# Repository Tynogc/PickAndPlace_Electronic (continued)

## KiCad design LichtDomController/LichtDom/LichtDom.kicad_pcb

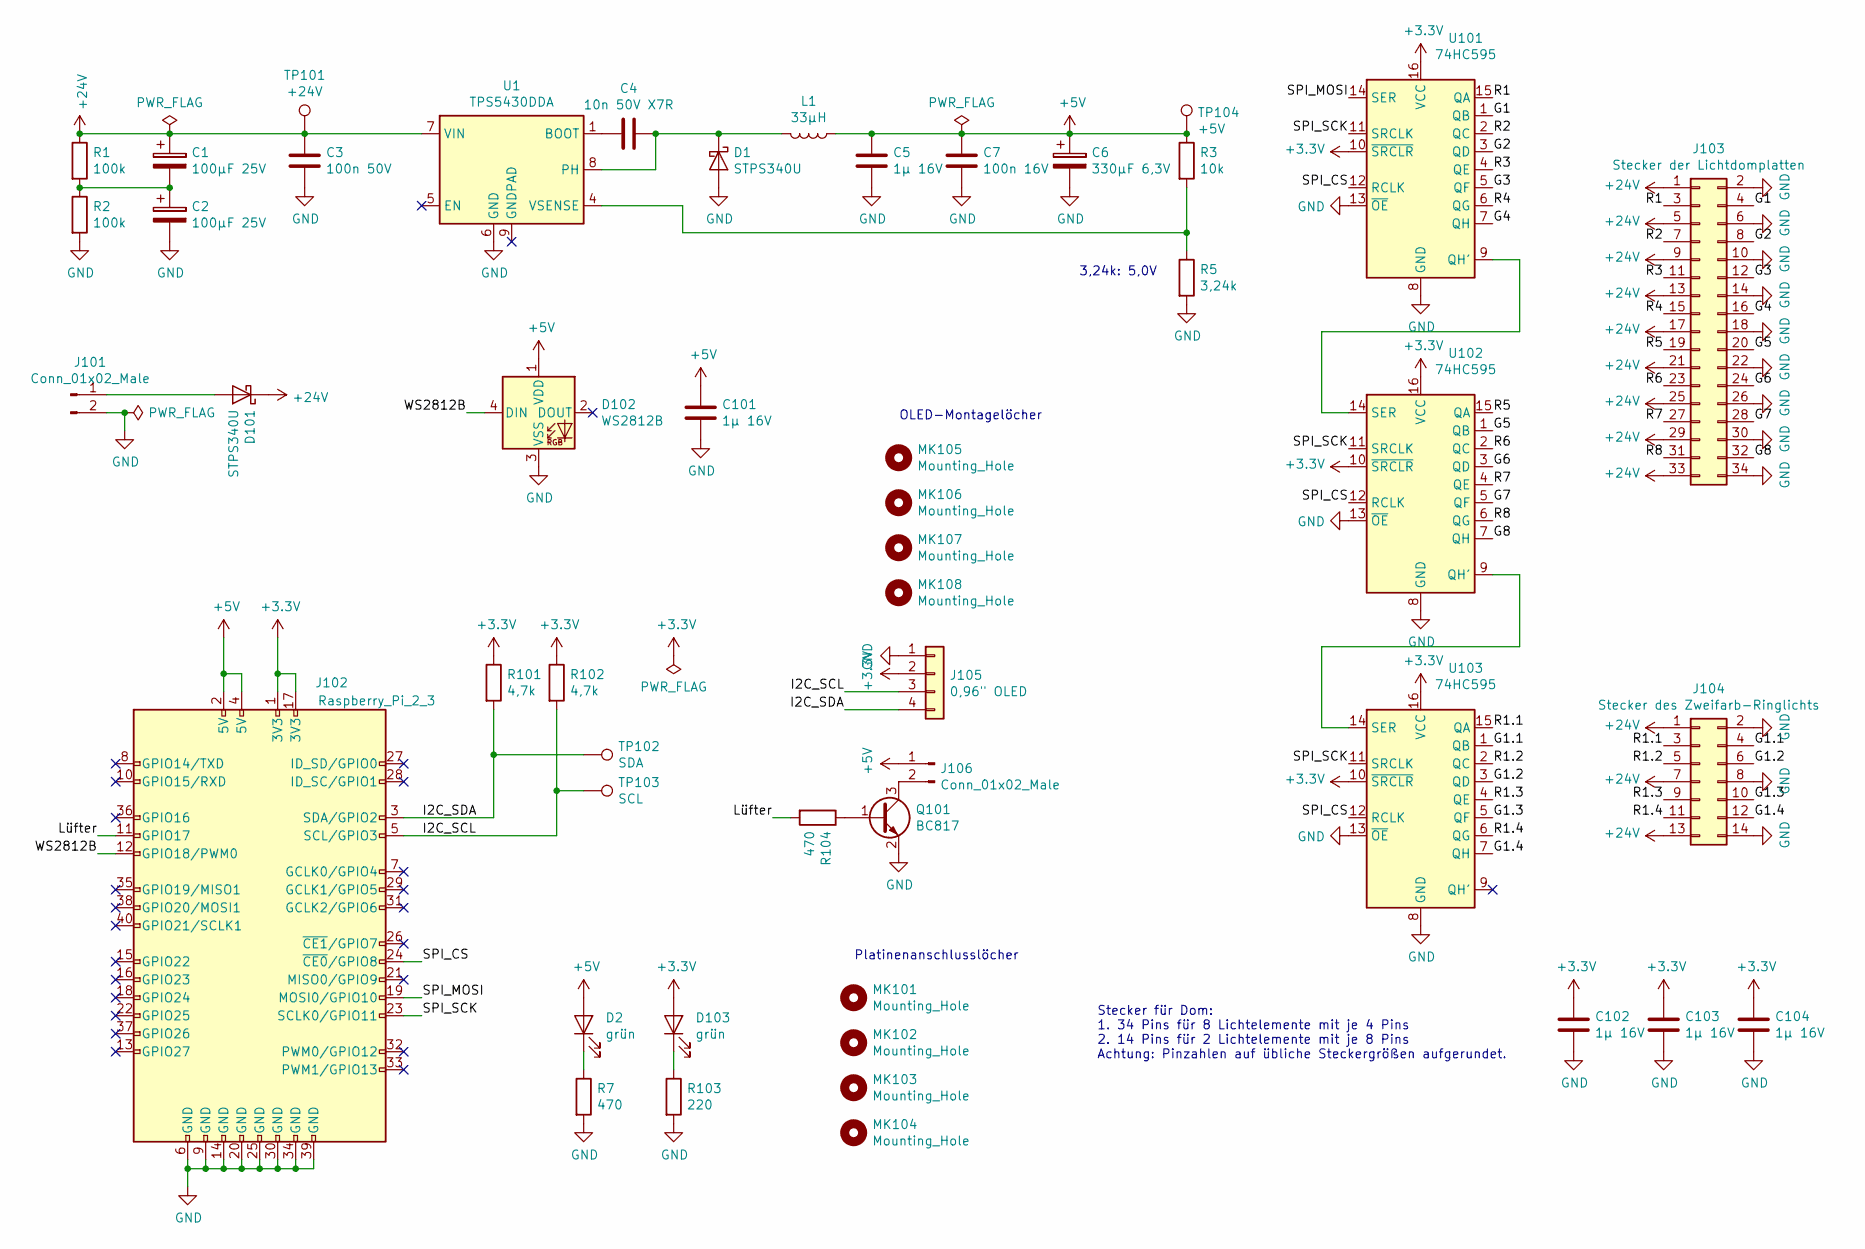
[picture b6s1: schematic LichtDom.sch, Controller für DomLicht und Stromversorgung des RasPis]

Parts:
C1, C2: 100µF 25V; CP_Elec_6.3x7.7
C3: 100n 50V; C_1206_3216Metric
C4: 10n 50V X7R; C_0603_1608Metric
C5, C101, C102, C103, C104: 1µ 16V; C_0805_2012Metric
C6: 330µF 6,3V; CP_Elec_6.3x7.7
C7: 100n 16V; C_0603_1608Metric
D1, D101: STPS340U; D_SMB
D2, D103: grün; LED_0603_1608Metric
D102: WS2812B; LED_WS2812B_PLCC4_5.0x5.0mm_P3.2mm
J101: Conn_01x02_Male; JST_XH_S02B-XH-A-1_1x02_P2.50mm_Horizontal
J102: Raspberry_Pi_2_3; PinSocket_2x20_P2.54mm_Horizontal
J103: Stecker der Lichtdomplatten; IDC-Header_2x17_P2.54mm_Horizontal
J104: Stecker des Zweifarb-Ringlichts; IDC-Header_2x07_P2.54mm_Horizontal
J105: 0,96\" OLED; PinSocket_1x04_P2.54mm_Vertical
J106: Conn_01x02_Male; JST_PH_S2B-PH-SM4-TB_1x02-1MP_P2.00mm_Horizontal
L1: 33µH; L_Wuerth_HCI-1040
MK101, MK102, MK103, MK104: Mounting_Hole; MountingHole_3.2mm_M3
MK105, MK106, MK107, MK108: Mounting_Hole; MountingHole_3.2mm_M3_DIN965
Q101: BC817; SOT-23
R1, R2: 100k; R_0603_1608Metric
R3: 10k; R_0603_1608Metric
R5: 3,24k; R_0603_1608Metric
R7, R104: 470; R_0603_1608Metric
R101, R102: 4,7k; R_0603_1608Metric
R103: 220; R_0603_1608Metric
TP101: +24V; TestPoint_Keystone_5005-5009_Compact
TP102: SDA; TestPoint_Keystone_5005-5009_Compact
TP103: SCL; TestPoint_Keystone_5005-5009_Compact
TP104: +5V; TestPoint_Keystone_5005-5009_Compact
U1: TPS5430DDA; SOIC-8_3.9x4.9mm_P1.27mm
U101, U102, U103: 74HC595; SOIC-16W_5.3x10.2mm_P1.27mm

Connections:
+3V3: C102.1, C103.1, C104.1, D103.2 (A), J102.1 (3V3), J102.17 (3V3), J105.2, R101.1, R102.1, U101.10 (~SRCLR), U101.16 (VCC), U102.10 (~SRCLR), U102.16 (VCC), U103.10 (~SRCLR), U103.16 (VCC)
+5V: C5.1, C6.1, C7.1, C101.1, D2.2 (A), D102.1 (VDD), J102.2 (5V), J102.4 (5V), J106.1, L1.1, R3.1, TP104.1
+24V: C1.1, C3.1, D101.1 (K), J103.1, J103.5, J103.9, J103.13, J103.17, J103.21, J103.25, J103.29, J103.33, J104.1, J104.7, J104.13, R1.1, TP101.1, U1.7 (VIN)
/G1: J103.4, U101.1 (QB)
/G1.1: J104.4, U103.1 (QB)
/G1.2: J104.6, U103.3 (QD)
/G1.3: J104.10, U103.5 (QF)
/G1.4: J104.12, U103.7 (QH)
/G2: J103.8, U101.3 (QD)
/G3: J103.12, U101.5 (QF)
/G4: J103.16, U101.7 (QH)
/G5: J103.20, U102.1 (QB)
/G6: J103.24, U102.3 (QD)
/G7: J103.28, U102.5 (QF)
/G8: J103.32, U102.7 (QH)
/I2C_SCL: J102.5 (SCL/GPIO3), J105.3, R102.2, TP103.1
/I2C_SDA: J102.3 (SDA/GPIO2), J105.4, R101.2, TP102.1
/Lüfter: J102.11 (GPIO17), R104.2
/R1: J103.3, U101.15 (QA)
/R1.1: J104.3, U103.15 (QA)
/R1.2: J104.5, U103.2 (QC)
/R1.3: J104.9, U103.4 (QE)
/R1.4: J104.11, U103.6 (QG)
/R2: J103.7, U101.2 (QC)
/R3: J103.11, U101.4 (QE)
/R4: J103.15, U101.6 (QG)
/R5: J103.19, U102.15 (QA)
/R6: J103.23, U102.2 (QC)
/R7: J103.27, U102.4 (QE)
/R8: J103.31, U102.6 (QG)
/SPI_CS: J102.24 (~CE0~/GPIO8), U101.12 (RCLK), U102.12 (RCLK), U103.12 (RCLK)
/SPI_MOSI: J102.19 (MOSI0/GPIO10), U101.14 (SER)
/SPI_SCK: J102.23 (SCLK0/GPIO11), U101.11 (SRCLK), U102.11 (SRCLK), U103.11 (SRCLK)
/WS2812B: D102.4 (DIN), J102.12 (GPIO18/PWM0)
GND: C2.2, C3.2, C5.2, C6.2, C7.2, C101.2, C102.2, C103.2, C104.2, D1.2 (A), D102.3 (VSS), J101.2, J102.6 (GND), J102.9 (GND), J102.14 (GND), J102.20 (GND), J102.25 (GND), J102.30 (GND), J102.34 (GND), J102.39 (GND), J103.2, J103.6, J103.10, J103.14, J103.18, J103.22, J103.26, J103.30, J103.34, J104.2, J104.8, J104.14, J105.1, Q101.2 (E), R2.2, R5.2, R7.2, R103.2, U1.6 (GND), U101.8 (GND), U101.13 (~OE), U102.8 (GND), U102.13 (~OE), U103.8 (GND), U103.13 (~OE)
unnamed: C1.2, C2.1, R1.2, R2.1
unnamed: C4.1, D1.1 (K), L1.2, U1.8 (PH)
unnamed: C4.2, U1.1 (BOOT)
unnamed: D2.1 (K), R7.1
unnamed: D101.2 (A), J101.1
unnamed: D103.1 (K), R103.1
unnamed: J106.2, Q101.3 (C)
unnamed: Q101.1 (B), R104.1
unnamed: R3.2, R5.1, U1.4 (VSENSE)
unnamed: U101.9 (QH'), U102.14 (SER)
unnamed: U102.9 (QH'), U103.14 (SER)

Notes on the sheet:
3,24k: 5,0V
Stecker für Dom: 1. 34 Pins für 8 Lichtelemente mit je 4 Pins 2. 14 Pins für 2 Lichtelemente mit je 8 Pins Achtung: Pinzahlen auf übliche Steckergrößen aufgerundet.
Platinenanschlusslöcher
OLED-Montagelöcher

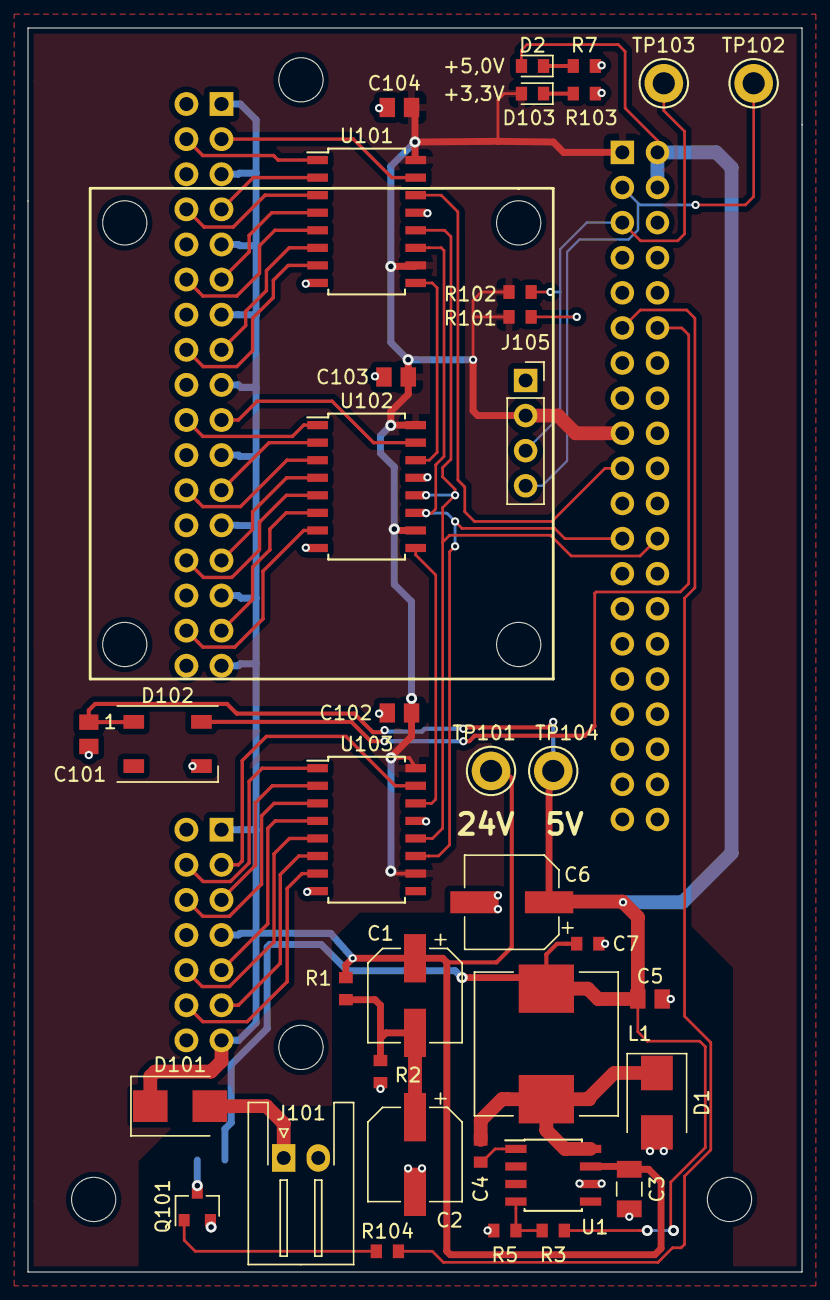
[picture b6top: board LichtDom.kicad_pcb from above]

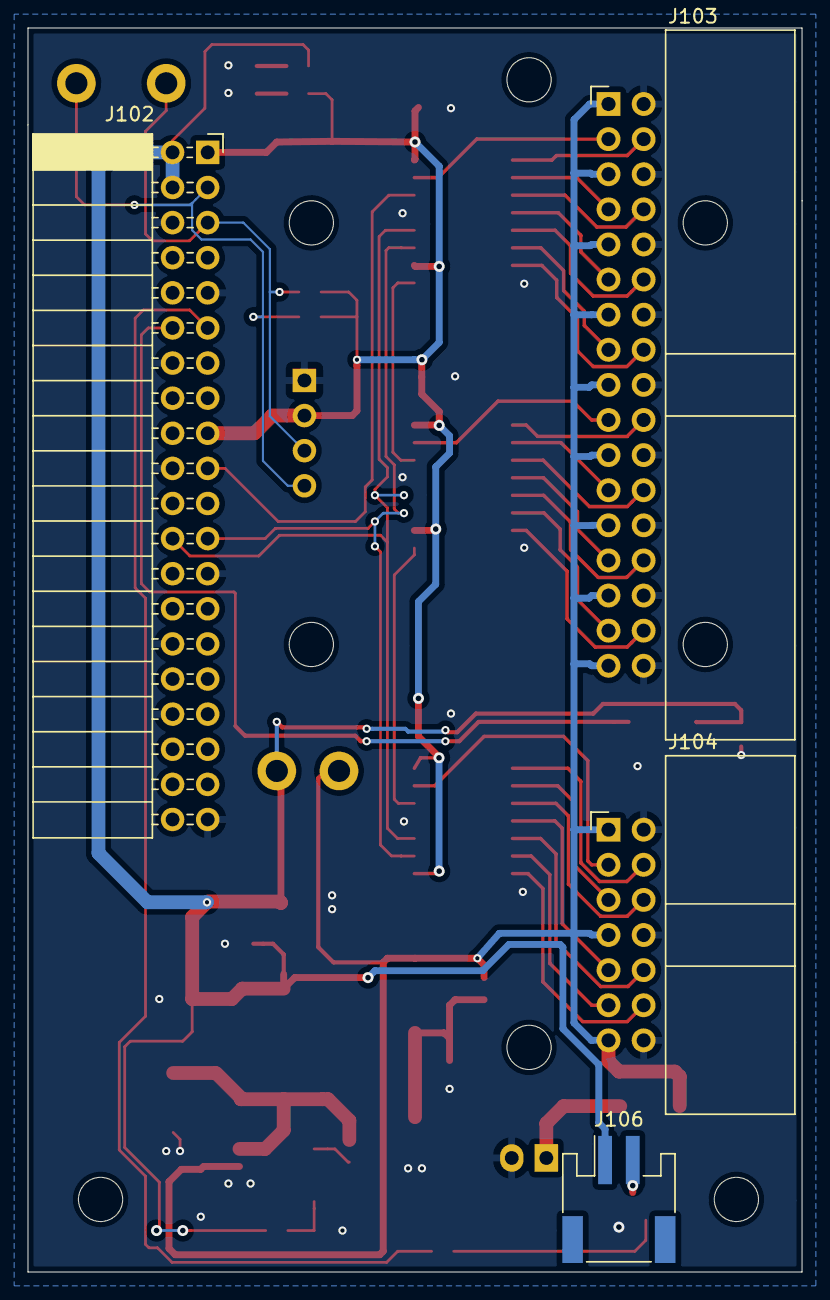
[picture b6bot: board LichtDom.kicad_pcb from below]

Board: 2 copper layers, 56.0 x 90.0 mm, 49 parts (4 on the bottom side), 46 nets.

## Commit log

2016-12-28 Added Project CameraLights
2017-02-03 ordner umbenannt und readme erweitert.
2017-02-03 Create LICENSE
2017-02-03 anfang des Feedercodes...
2017-02-03 led blinkt, taster geht. ws2812 integration hat angefangen...
2017-02-04 integration der WS2812 im Gange, noch keine Funktion. defines recht weit.
2017-02-08 neue Datenblätter
2017-02-08 eclipse-Code hinzugefügt. LED geht, am Motor bin ich dran.
2017-02-08 Matlabprogramm zur Berechnung einer Schrittmotorfahrt hinzugefügt - UNFERTIG
2017-02-24 Camera-Lights-Final
2017-02-25 Schaltplan und Netzliste für Testboard erstellt
2017-02-25 code verlinkt statt direkt eingebungen.. versuche
2017-02-25 defines.h wiederhergestellt
2017-03-04 code als submodul hinzugefügt
2017-03-05 Bahnplanung weitergemacht/simuliert und mehr Matlab-code geschrieben... STM32 Code ausgelagert in Submodule
2019-11-30 neues Pr0jekt DomController hinzugefügt. Aktuell nur Schaltplan
2019-11-30 beginn vom pcb hinzugefügt...
2019-12-02 Kopf-LED-Ring hinzugefügt
2019-12-02 Controller grobe Abmessungen fertig
2019-12-03 Dom-Controller OLED gesetzt
2019-12-03 Seltsame KiCad-Sachen
    fp-info-cach hat sich stark geändert, muss evtl. reverted werden.
    Ausserdem wurde das Autosave gelöscht.
2019-12-04 Datenblatt des Schieberegisters und erste 3D-Daten fehlender Bauteile hinzugefügt
2019-12-04 Layout quasi fertig - Texte ausgerichtet. Teilweise fehlen noch 3D-Daten!
2019-12-04 24V ordentlicher gemacht.
2019-12-05 Temperatursensor hinzugefügt
2019-12-06 Lüfteranschluss hinzufügt.
2019-12-06 LichtDom LED-Panels hinzugefügt
2019-12-06 EdgCuts gezeichnet
2019-12-06 Silkscreen aufgeräumt
2019-12-09 Ordner LichtDom_Hex umbenannt in LichtDom_SidePanels.
2019-12-10 Alten Plan entfernt
2019-12-10 Gabellichtschranken-Test-PCB hinzugefügt
2019-12-10 Gerber Export, richtige Einstellungen im KiCad PCB Export hinterlegt
2019-12-10 Gerber hinzugefügt und Einstellungen aktualsiert
2019-12-11 Export Optionen waren nicht richtig gesetzt
2019-12-11 Fertigungsstand 10.12.19 hinzugefügt
2019-12-29 STEP Daten für LichtDom hinzugefügt
2020-01-08 neue Datenblätter, Wärmebilder vom weißen LichtRing und Software für den ComController
2020-01-18 DomController Software hinzugefügt...
2020-01-18 Datenprotokoll v0.1 hinzugefügt, SocketServer für LichtDom angefangen
2020-01-20 TCP Verbindung weiter geschrieben
2020-01-26 Logging, Argumente hinzugefügt - Handling von SIGINT verbessert
2020-01-26 Python3 Anpassungen vorgenommen
2020-02-09 conf für den supervisor des Control-Raspis hinzugefügt
